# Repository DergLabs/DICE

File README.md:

# DICE - Dynamic Image Compression Engine
<ins>Developed by John Hofmeyr, Claudia Oufft, Michael Haahr, Shahriyar Shawon, Oscar Balan</ins>

*Drexel University Senior Class of 2025*

*Developed under the guidance of Dr. Anup Das*

<ins>**Overview**</ins>

The goal of this project was to develop a hardware based image processing system and hybrid file format that would take advantage of the benefits from both lossy and lossless image compression. 

By utilizing tiling, different image compression formats can be applied throughout an image based on the content of the tile. Improved image quality can be obtained when comapred to fully lossy compression, while maintaining file sizes smaller than that of fully lossless images. Our proposed solution utilizes a hardware optimized JPEG encoder for lossy compression and a novel hardware optimized arithmetic encoder for lossless compression.

<ins>**Implementation**</ins>

Image files are loaded and pre-processed into a pixel datastream using the Dice Reference compression tool. Image pre-processing consists of extracting the R, G and B channels from the image, applying matrix folding to create the 32x32 pixel tiles, and finally creating the byte arrays of raw pixels to be sent to the FPGA via USB. 

The FT600 USB FIFO is used to send and receive image data. Raw image data is sent to the FPGA module and loaded into a CDC FIFO buffer. The buffer stores 4KB of pixel data (equivalent to a 32x32 tile using 32b per pixel (8b for R, G, B and one spare byte to simplify processing). 

The pixels are then sent to the hardware statistics core to compute the mean, variance and std. deviation of the Laplacian and X/Y gradient kernels. The Variance of the Laplacian kernel values provides a numerical value that quantifies the blurryness of the tile while the mean and std. deviation of the 2d X/Y gradient values provide an indication of large changes in contrast, color or sharp edges in the tile. This information is used to determine what compression method should be used based on pre-defined threshold values. 

While the tile statistics are calculated, the pixel data is sent to both the Lossy and Lossless compression cores, with the processed data being buffered in output hold ram. Once the compression determination is made, the output data streams from both hold rams are muxed, selecting only one to be transmitted back to the FT600. 

<ins>**Hardware Platform**</ins> 

A dual board hardware platform was developed for this project. The hardware architecture is split into two modules, the IO moduel and FPGA module. The IO module provides video connectivity, high speed USB connectivity, USB-PD power control and monitoring, and Debug/JTAG IO. Below is a list of all IO available: 

- 4 Lane MIPI CSI (upto 2Gb/s per lane)
- HDMI 2.0 (Upto 4K 30FPS via Sii1136)
- USB 3.0 5Gb/s to FT600
- 3x USB 2.0 (1x for RP2040, 1x for FT2232, 1x for FPGA module MCU)
- Configurable USB-PD control allowing for upto 15V 5A
- Voltage, Current, Power & Temperature monitoring
- UART & JTAG for FPGA
- 12x GPIOs from RP2040 MCU to FPGA
- 16-bit USB FIFO Bus to FPGA (upto 1Gb/s)

The FPGA Module provides all of the processing hardware and implements the custom designed image processor. A Xilinx Kintex Ultrascale+ KU3P was utilized. Two DC-DC converters generate all voltage rails, the TDA38840 provides 0.85V at upto 40A for the FPGA VCCINT, and an LT7200 is used to generate 3.3V, 5V, 1.8V and 1.2V at 3A per channel. All rails have voltage, current, power and temperature monitoring. An onboard 200MHz oscillator provides the main system clock for the FPGA. Four 512Mb HyperRam 3.0 memory modules are also present. Each memory chip provides a 16-bit 250MHz DDR bus. The memory chips have been routed to allow for two banks of two chips each with length matching between chips 0/1 and 2/3. 

<ins>**Hardware Architecture**</ins>

The harware platform is split between two modules; the IO module and the FPGA module. The IO module contains all user IO, USB Power handling and supporting interface hardware. The FPGA module contains the Kintex US+ KU3P FPGA, 4x HyperRam modules, power supplies, FPGA clock, and onboard microcontroller. 

*IO Module Specifications*
- USB-C 3.0 Data & Power Port, supports 5Gb/s USB & USB-PD 2.1 (upto 20V 5A)
- 4 lane MIPI CSI
- HDMI 1.4b, supports 4K30
- FT600 USB FIFO, supports 1Gb/s bandwidth over 16-bit bus
- FT2232 confgired for JTAG and UART
- RP2040 for data logging & control

*FPGA Module Specifications*
- Kintex Ultrascale+ KU3P FPGA
- 4x HyperRam 3.0 512Mb
- RP2040 MCU
- LT7200S DC-DC (1.8v, 1.2v, 3.3v, 5v at 3A each)
- TDA38840A DC-DC (0.85V VCCINT at 40A)
- INA700 power monitors on 1.8v, 1.2v, 3.3v
- INA236 power monitor on 0.85V
- 4x User LED's
- 8x GPIO debug pads
- 200MHz System Clock
- 256Mb configuration memory

The following diagram outlines the top level hardware configuration:

<ins>**Lossy Compression Architecture**</ins>

The lossy compression method implemented for this design is a hardware optimized version of JPEG encoding. The JPEG implementation has been designed to work on 8 pixels per clock cycle, using a serial-to-parallel input register to convert the serial pixel input stream into 8 parallel pixel streams. The simplified architecture for the lossy core is shown below.

In addition to the JPEG compression core, RGB to YCrCb conversion is performed. The implementation for this is shown below.

In order to determine which compression method to utilize, statistics from the gradient and laplacian kernels is used. The current implementation uses the variance of the X/Y gradient and Laplacian convolutions. Variance was chosen as it provides a good representation of texture, edge transitions, and blur. The implementation of the gradient and laplacian calculations are shown below. Note, only the X sobel computation is shown, however the Y computation is identical.

<ins>Laplacian Core</ins>

<ins>Gradient Core</ins>

<ins>**Lossless Compression Architecture**</ins>

<ins>Arithmetic Encoder Core</ins>

For the lossless compression core, a running count adaptive model is used since arithmetic encoding can achieve a higher compression ratio using applicable adaptive models. Data can be ingested and processed at a rate of one byte per clock cycle. A binary tree for storing symbol probability ranges was chosen to reduce the lookup time for the lower bound of the range to O(lg(n)), where n is the bit-width of the symbol. Choosing 8 bits as the symbol size was done to ensure large enough symbols could be processed by the arithmetic compression core, but would not be so large as to make the size of the binary tree for storing the probability ranges of each symbol too big. 

A data dependency between the upper and lower working range of the encoder and the output of the final renormalization stages of the pipeline could result in stalling for several clock cycles while waiting for the updated ranges. Some reorganization and consolidation of the pipeline was done to reduce the length of this dependency in the pipeline, such as moving the division step of the new bounds calculation before this critical path, and reducing the renormalization steps to take one cycle each. The final step employed to overcome stalling in the critical path of the arithmetic coding pipeline is to use multiple working bounds. This effectively strobes the data into multiple compression streams that share the same pipeline, negating the need to stall as long as the number of streams is higher than the number of pipeline stages in the critical path.

A top level architecture diagram of the arithemetic encoder is shown below.

<ins>**Software Tools**</ins>

Two main software tools are used; the serial communications tool, and the reference compression tool. 

The serial communications tool provides a serial terminal for connecting to the onboard microcontrollers. This terminal displays important hardware metrics including board temperatures, voltages, currents and power of the various power rails. 

The reference compression tool is used to test and use the DICE hardware. This tool allows users to load in an image, set gradient and laplacian threshold values, format and transfer image data to the FPGA, decode recieved image data, create and save the DICE image files, and display the DICE compressed image with relevant statistics such as PSNR, MS-SSIM, file size and lossy/lossless tile metrics. 

<ins>**DICE File Format**</ins>

The DICE file format is broken into three main sections; the main file header, the lossless header and lossless data, and the lossy header and lossy data. The main file header contains general file information, decoding and dequantization tables as well as the tile ID grid used to identify the location and ID of each image tile. The lossy and lossless headers provide information about the number of tiles, and the size of each tile. All tiles are formatted to be the same size for simplicity sake, however future improvements would include allowing for variable tile sizes to reduce file size. Finally, the lossless tiles are stored as arithmetic encoded R, G and B arrays while the Lossy data is stored as quantized Y, Cr and Cb arrays. The diagram below shows the full file format.

<ins>DICE File Format</ins>

<ins>**Research Papers & References**</ins>

The following research papers and references were used during the development of this project.

[1] Jonathan Griffin,
“The Ultimate Guide to JPEG including JPEG Compression & Encoding”
www.thewebmaster.com. https://www.thewebmaster.com/jpeg-definitive-guide/

‌
[2]H. Anas, “Fast 8*8*8 RCF 3D_DCT/IDCT transform for real time video compression and its FPGA Implementation,” vol. volume 7, no. 2, May 2014, https://www.researchgate.net/publication/262896207_Fast_888_RCF_3D_DCTIDCT_transform_for_real_time_video_compression_and_its_FPGA_Implementation
‌

[3]H. Anas, Said Belkouch, M. El Aakif, and Noureddine Chabini, “FPGA implementation of a pipelined 2D-DCT and simplified quantization for real-time applications,” International Conference on Multimedia Computing and Systems, pp. 1–6, Apr. 2011, doi: https://doi.org/10.1109/icmcs.2011.5945659.
‌

[4]S. Sudiro, A. Kardian, S. Madenda, and L. Hermanto, “OPEN ACCESS Mean and variance statistic for image processing on FPGA,” vol. 115, no. 1, p. 2020115, doi: https://doi.org/10.6703/IJASE.202103_18(1).115.
‌

‌[5] Mark Nelson,
“Data Compression With Arithmetic Coding”, Mark Nelson, Oct. 19, 2014.
https://marknelson.us/posts/2014/10/19/data-compression-with-arithmetic-coding.html 

‌[6] Mark Nelson,
“Arithmetic Coding + Statistical Modeling = Data Compression”, Mark Nelson, Feb. 1, 1991.
https://marknelson.us/posts/1991/02/01/arithmetic-coding-statistical-modeling-data-compression

‌[7] Wikipedia Contributors,
“Discrete Cosine Transform”, Wikipedia,
https://en.wikipedia.org/wiki/Discrete_cosine_transform# 

[8] Wikipedia Contributors,
“Huffman Coding”, Wikipedia,
https://en.wikipedia.org/wiki/Huffman_coding 
‌

‌[9]
“LZSS” The Hitchhiker’s Guide to Compression, 2024.
https://go-compression.github.io/algorithms/lzss/

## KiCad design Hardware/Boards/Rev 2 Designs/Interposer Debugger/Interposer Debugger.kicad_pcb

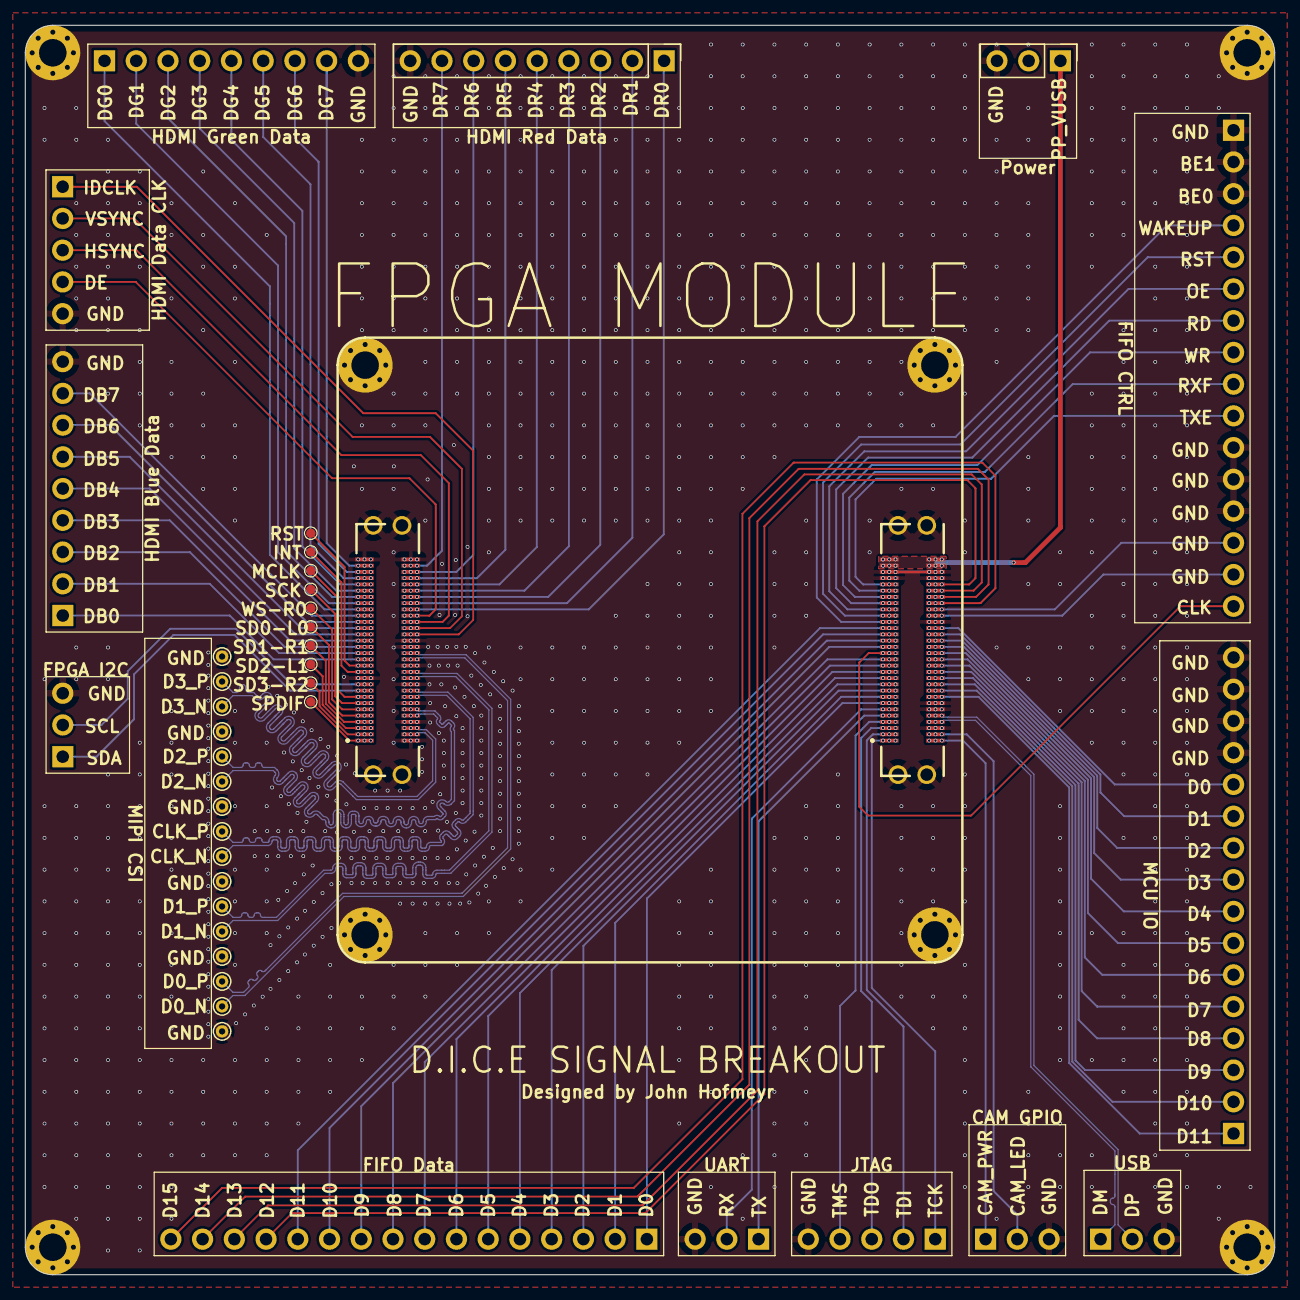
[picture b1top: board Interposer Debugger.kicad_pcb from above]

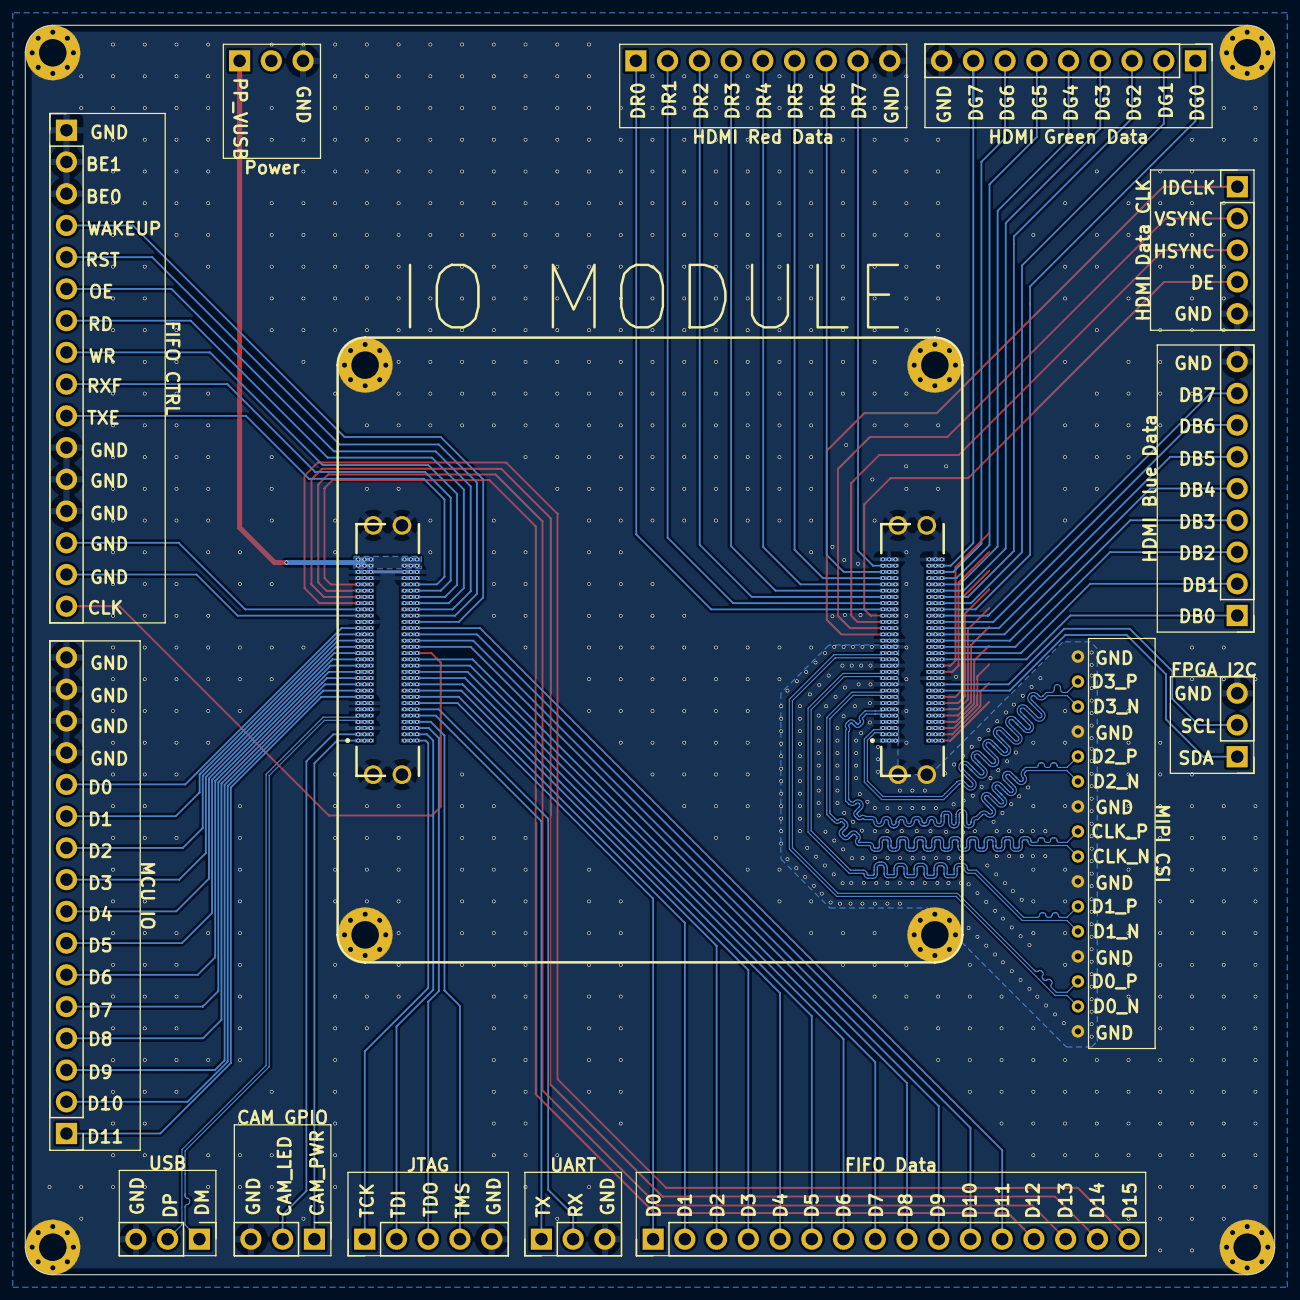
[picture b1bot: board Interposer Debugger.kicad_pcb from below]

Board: 4 copper layers, 100.0 x 100.0 mm, 51 parts (13 on the bottom side), 100 nets.

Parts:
J1, J16: Conn_01x05; PinHeader_1x05_P2.54mm_Vertical
J2, J3, J4, J5: LSHM-130-XX.X-XXX-DV-A-S-K-XX; SAMTEC_LSHM-130-XX.X-XXX-DV-A-S-K-XX
J7, J14, J19, J21, J22: Conn_01x03; PinHeader_1x03_P2.54mm_Vertical
J8, J23, J24: Conn_01x16; PinHeader_1x16_P2.54mm_Vertical
J9, J12, J13: Conn_01x09; PinHeader_1x09_P2.54mm_Vertical
TP1, TP2, TP3, TP4: Mounting Hole; MountingHole_2.2mm_M2_Pad_Via
TP5, TP6, TP7#2, TP8, TP9#2, TP10, TP11, TP12, TP13, TP14: TestPoint; Test Point 0.75mm
TP6#2, TP7, TP8#2, TP9: MH; MountingHole_2.2mm_M2_Pad_Via
TP15, TP16, TP17, TP18, TP19, TP20, TP21, TP22, TP23, TP24, TP25, TP26, TP27, TP28, TP29, TP30: TestPoint; TestPoint_THTPad_D1.0mm_Drill0.5mm

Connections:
/CAM_LED_EN: J3.04, J5.03, J19.2
/CAM_PWR_EN: J3.02, J5.01, J19.1
/FIFO_BE0: J3.44, J5.43, J23.14
/FIFO_BE1: J3.42, J5.41, J23.15
/FIFO_CLK: J3.29, J5.30, J23.16
/FIFO_D0: J3.13, J5.14, J8.1
/FIFO_D1: J3.15, J5.16, J8.2
/FIFO_D2: J3.17, J5.18, J8.3
/FIFO_D3: J3.19, J5.20, J8.4
/FIFO_D4: J3.21, J5.22, J8.5
/FIFO_D5: J3.23, J5.24, J8.6
/FIFO_D6: J3.25, J5.26, J8.7
/FIFO_D7: J3.27, J5.28, J8.8
/FIFO_D8: J3.31, J5.32, J8.9
/FIFO_D9: J3.33, J5.34, J8.10
/FIFO_D10: J3.35, J5.36, J8.11
/FIFO_D11: J3.37, J5.38, J8.12
/FIFO_D12: J3.52, J5.51, J8.13
/FIFO_D13: J3.50, J5.49, J8.14
/FIFO_D14: J3.48, J5.47, J8.15
/FIFO_D15: J3.46, J5.45, J8.16
/FPGA_I2C_SCL: J2.19, J4.20, J14.2
/FPGA_I2C_SDA: J2.17, J4.18, J14.1
/FT600_OE: J3.47, J5.48, J23.8
/FT600_RD: J3.45, J5.46, J23.7
/FT600_RST: J3.49, J5.50, J23.9
/FT600_RXE: J3.41, J5.42, J23.5
/FT600_TXE: J3.39, J5.40, J23.4
/FT600_WAKEUP: J3.51, J5.52, J23.10
/FT600_WR: J3.43, J5.44, J23.6
/HDMI_DB0: J2.27, J4.28, J13.1
/HDMI_DB1: J2.29, J4.30, J13.2
/HDMI_DB2: J2.31, J4.32, J13.3
/HDMI_DB3: J2.33, J4.34, J13.4
/HDMI_DB4: J2.35, J4.36, J13.5
/HDMI_DB5: J2.37, J4.38, J13.6
/HDMI_DB6: J2.39, J4.40, J13.7
/HDMI_DB7: J2.41, J4.42, J13.8
/HDMI_DE: J2.42, J4.41, J16.4
/HDMI_DG0: J2.43, J4.44, J12.1
/HDMI_DG1: J2.45, J4.46, J12.2
/HDMI_DG2: J2.47, J4.48, J12.3
/HDMI_DG3: J2.49, J4.50, J12.4
/HDMI_DG4: J2.51, J4.52, J12.5
/HDMI_DG5: J2.53, J4.54, J12.6
/HDMI_DG6: J2.55, J4.56, J12.7
/HDMI_DG7: J2.57, J4.58, J12.8
/HDMI_DR0: J2.44, J4.43, J9.1
/HDMI_DR1: J2.46, J4.45, J9.2
/HDMI_DR2: J2.48, J4.47, J9.3
/HDMI_DR3: J2.50, J4.49, J9.4
/HDMI_DR4: J2.52, J4.51, J9.5
/HDMI_DR5: J2.54, J4.53, J9.6
/HDMI_DR6: J2.56, J4.55, J9.7
/HDMI_DR7: J2.58, J4.57, J9.8
/HDMI_HSYNC: J2.40, J4.39, J16.3
/HDMI_IDCLK: J2.36, J4.35, J16.1
/HDMI_INT: J2.23, J4.24, TP13.1
/HDMI_MCLK: J2.15, J4.16, TP12.1
/HDMI_RST: J2.25, J4.26, TP14.1
/HDMI_SCK: J2.13, J4.14, TP11.1
/HDMI_SD0_DL0: J2.09, J4.10, TP9#2.1
/HDMI_SD1_DR1: J2.07, J4.08, TP8.1
/HDMI_SD2_DL1: J2.05, J4.06, TP7#2.1
/HDMI_SD3_DR2: J2.03, J4.04, TP6.1
/HDMI_SPDIF: J2.01, J4.02, TP5.1
/HDMI_VSYNC: J2.38, J4.37, J16.2
/HDMI_WS_DR0: J2.11, J4.12, TP10.1
/JTAG_TCK: J1.1, J3.01, J5.02
/JTAG_TDI: J1.2, J3.03, J5.04
/JTAG_TDO: J1.3, J3.05, J5.06
/JTAG_TMS: J1.4, J3.07, J5.08
/MBUS_D0: J3.38, J5.37, J24.12
/MBUS_D1: J3.36, J5.35, J24.11
/MBUS_D2: J3.34, J5.33, J24.10
/MBUS_D3: J3.32, J5.31, J24.9
/MBUS_D4: J3.30, J5.29, J24.8
/MBUS_D5: J3.28, J5.27, J24.7
/MBUS_D6: J3.26, J5.25, J24.6
/MBUS_D7: J3.24, J5.23, J24.5
/MBUS_D8: J3.22, J5.21, J24.4
/MBUS_D9: J3.20, J5.19, J24.3
/MBUS_D10: J3.18, J5.17, J24.2
/MBUS_D11: J3.16, J5.15, J24.1
/MIPI_CLK_N: J2.18, J4.17, TP23.1
/MIPI_CLK_P: J2.16, J4.15, TP22.1
/MIPI_D0_N: J2.30, J4.29, TP29.1
/MIPI_D0_P: J2.28, J4.27, TP28.1
/MIPI_D1_N: J2.24, J4.23, TP26.1
/MIPI_D1_P: J2.22, J4.21, TP25.1
/MIPI_D2_N: J2.12, J4.11, TP20.1
/MIPI_D2_P: J2.10, J4.09, TP19.1
/MIPI_D3_N: J2.06, J4.05, TP17.1
/MIPI_D3_P: J2.04, J4.03, TP16.1
/PP_VUSB: J3.57, J3.58, J3.59, J3.60, J5.57, J5.58, J5.59, J5.60, J7.1
/UART_RX: J3.11, J5.12, J21.2
/UART_TX: J3.09, J5.10, J21.1
/USB_SYSMON_D_N: J3.08, J5.07, J22.1
/USB_SYSMON_D_P: J3.10, J5.09, J22.2
GND: J1.5, J2.02, J2.08, J2.14, J2.20, J2.21, J2.26, J2.32, J2.34, J2.59, J2.60, J2.S1 (SHIELD), J2.S2 (SHIELD__1), J3.06, J3.12, J3.14, J3.40, J3.53, J3.54, J3.55, J3.56, J3.S1 (SHIELD), J3.S2 (SHIELD__1), J4.01, J4.07, J4.13, J4.19, J4.22, J4.25, J4.31, J4.33, J4.59, J4.60, J4.S1 (SHIELD), J4.S2 (SHIELD__1), J5.05, J5.11, J5.13, J5.39, J5.53, J5.54, J5.55, J5.56, J5.S1 (SHIELD), J5.S2 (SHIELD__1), J7.3, J9.9, J12.9, J13.9, J14.3, J16.5, J19.3, J21.3, J22.3, J23.1, J23.2, J23.3, J23.11, J23.12, J23.13, J24.13, J24.14, J24.15, J24.16, TP1.1, TP2.1, TP3.1, TP4.1, TP6#2.1, TP7.1, TP8#2.1, TP9.1, TP15.1, TP18.1, TP21.1, TP24.1, TP27.1, TP30.1

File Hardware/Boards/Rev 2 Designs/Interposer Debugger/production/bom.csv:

Designator,Footprint,Quantity,Value,LCSC Part #
"J1, J16",PinHeader_1x05_P2.54mm_Vertical,2,Conn_01x05,
"J12, J13, J9",PinHeader_1x09_P2.54mm_Vertical,3,Conn_01x09,
"J14, J19, J21, J22, J7",PinHeader_1x03_P2.54mm_Vertical,5,Conn_01x03,
"J2, J3, J4, J5",SAMTEC_LSHM-130-XX.X-XXX-DV-A-S-K-XX,4,LSHM-130-XX.X-XXX-DV-A-S-K-XX,
"J23, J24, J8",PinHeader_1x16_P2.54mm_Vertical,3,Conn_01x16,
"TP1, TP2, TP3, TP4",MountingHole_2.2mm_M2_Pad_Via,4,Mounting Hole,
"TP10, TP11, TP12, TP13, TP14, TP5, TP6_2, TP7, TP8_2, TP9",Test Point 0.75mm,10,TestPoint,
"TP15, TP16, TP17, TP18, TP19, TP20, TP21, TP22, TP23, TP24, TP25, TP26, TP27, TP28, TP29, TP30",TestPoint_THTPad_D1.0mm_Drill0.5mm,16,TestPoint,
"TP6, TP7_2, TP8, TP9_2",MountingHole_2.2mm_M2_Pad_Via,4,MH,

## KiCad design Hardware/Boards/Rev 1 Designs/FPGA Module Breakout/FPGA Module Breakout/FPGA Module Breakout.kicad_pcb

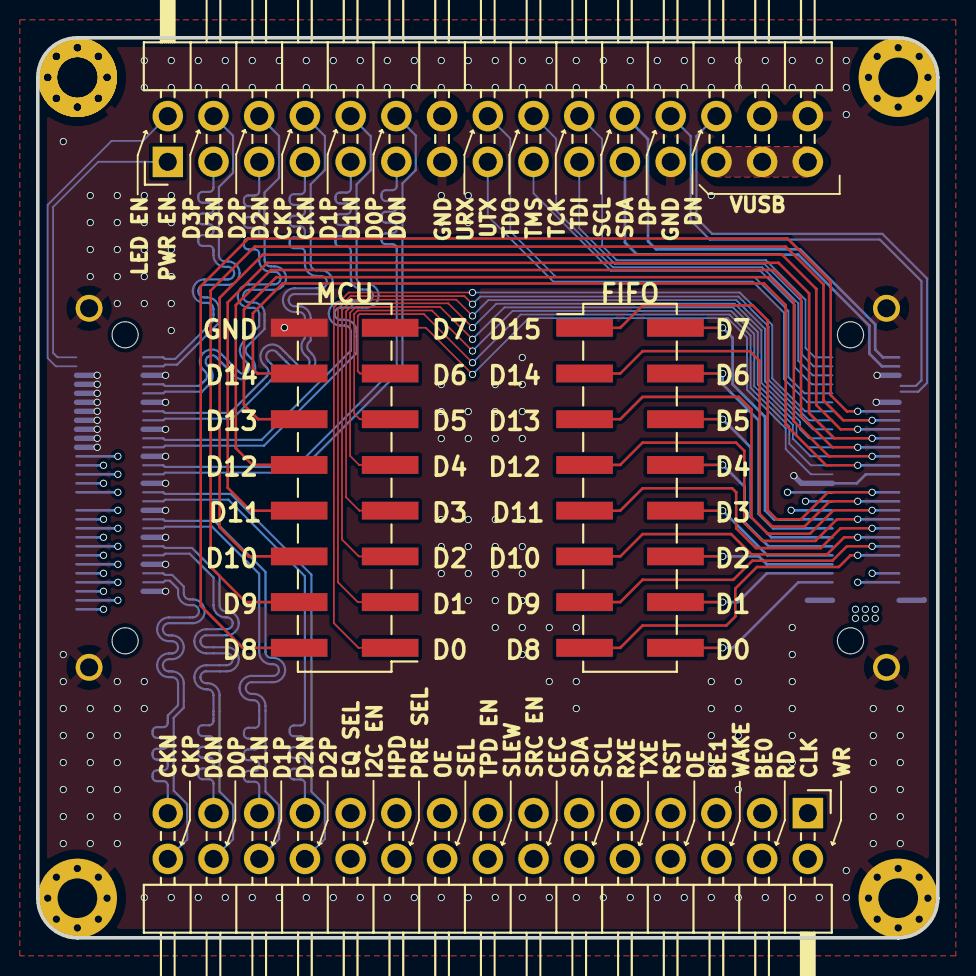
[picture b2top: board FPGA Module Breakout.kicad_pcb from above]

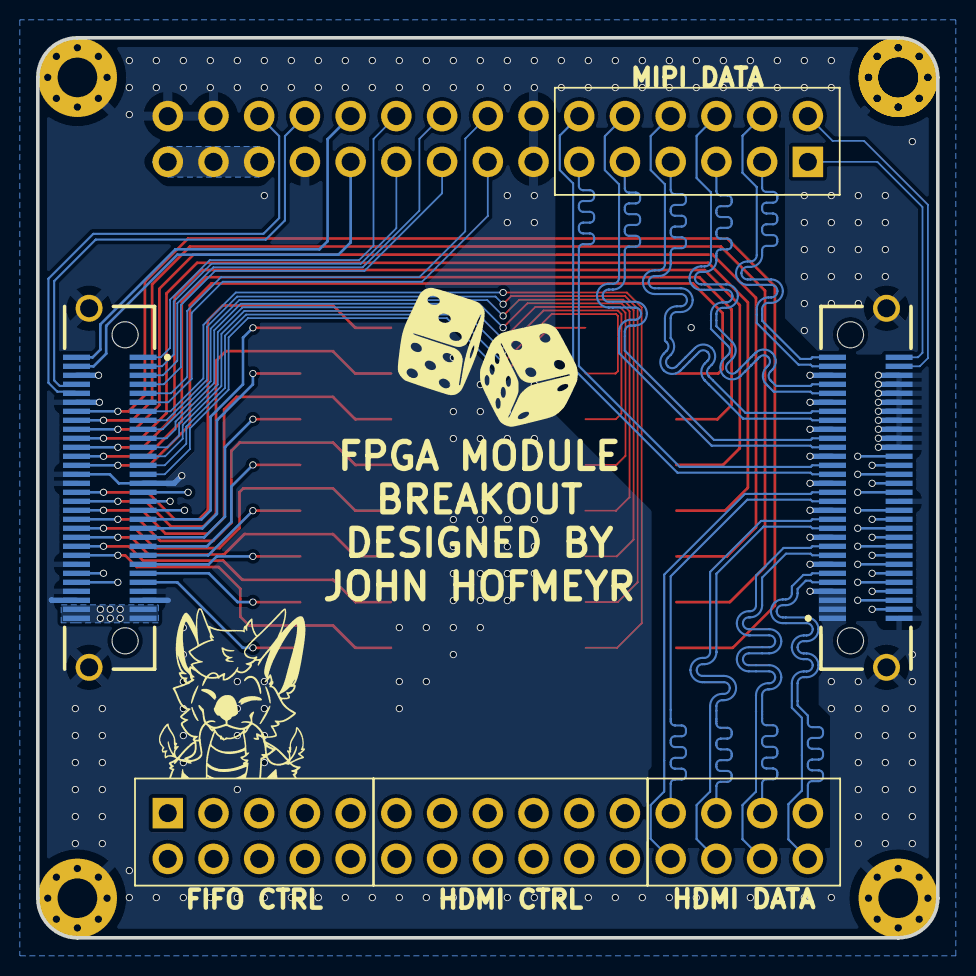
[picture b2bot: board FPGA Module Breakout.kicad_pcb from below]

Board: 4 copper layers, 50.0 x 50.0 mm, 11 parts (2 on the bottom side), 85 nets.

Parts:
J1, J2: LSHM-130-XX.X-XXX-DV-A-S-K-XX; SAMTEC_LSHM-130-XX.X-XXX-DV-A-S-K-XX
J3, J18: Conn_02x08_Odd_Even; PinHeader_2x08_P2.54mm_Vertical_SMD
J4, J5: Conn_02x15_Odd_Even; PinHeader_2x15_P2.54mm_Horizontal
PCB: Mounting Hole; MountingHole_2.2mm_M2_Pad_Via
TP1, TP2, TP3, TP4: Mounting Hole; MountingHole_2.2mm_M2_Pad_Via

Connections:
/CAM_LED_EN: J1.58, J5.2
/CAM_PWR_EN: J1.60, J5.1
/FIFO_BE0: J2.33, J4.3
/FIFO_BE1: J2.31, J4.5
/FIFO_CLK: J2.35, J4.1
/FIFO_D0: J2.51, J18.16
/FIFO_D1: J2.49, J18.14
/FIFO_D2: J2.47, J18.12
/FIFO_D3: J2.45, J18.10
/FIFO_D4: J2.43, J18.8
/FIFO_D5: J2.41, J18.6
/FIFO_D6: J2.39, J18.4
/FIFO_D7: J2.37, J18.2
/FIFO_D8: J2.46, J18.15
/FIFO_D9: J2.44, J18.13
/FIFO_D10: J2.42, J18.11
/FIFO_D11: J2.40, J18.9
/FIFO_D12: J2.38, J18.7
/FIFO_D13: J2.36, J18.5
/FIFO_D14: J2.34, J18.3
/FIFO_D15: J2.32, J18.1
/FPGA_I2C_SCL: J2.02, J5.22
/FPGA_I2C_SDA: J2.04, J5.21
/FT600_OE: J1.34, J4.8
/FT600_RD: J2.50, J4.4
/FT600_RST: J1.36, J4.7
/FT600_RXE: J1.32, J4.9
/FT600_TXE: J1.30, J4.10
/FT600_WAKEUP: J1.38, J4.6
/FT600_WR: J2.52, J4.2
/HDMI_CEC: J1.20, J4.14
/HDMI_CLK_N: J1.09, J4.29
/HDMI_CLK_P: J1.11, J4.30
/HDMI_D0_N: J1.15, J4.27
/HDMI_D0_P: J1.17, J4.28
/HDMI_D1_N: J1.21, J4.25
/HDMI_D1_P: J1.23, J4.26
/HDMI_D2_N: J1.27, J4.23
/HDMI_D2_P: J1.29, J4.24
/HDMI_EQ_SEL: J1.06, J4.21
/HDMI_HPD_SRC: J1.10, J4.19
/HDMI_I2C_EN: J1.04, J4.22
/HDMI_OE: J1.14, J4.17
/HDMI_PRE_SEL: J1.08, J4.20
/HDMI_SCL_SRC: J1.24, J4.12
/HDMI_SDA_SRC: J1.26, J4.11
/HDMI_SDA_SRC_EN: J1.22, J4.13
/HDMI_SEL: J1.12, J4.18
/HDMI_SLEW_CTL: J1.16, J4.16
/JTAG_TCK: J2.01, J5.20
/JTAG_TDI: J2.03, J5.19
/JTAG_TDO: J2.05, J5.18
/JTAG_TMS: J2.07, J5.17
/MBUS_D0: J2.13, J3.1
/MBUS_D1: J2.15, J3.3
/MBUS_D2: J2.17, J3.5
/MBUS_D3: J2.19, J3.7
/MBUS_D4: J2.21, J3.9
/MBUS_D5: J2.23, J3.11
/MBUS_D6: J2.25, J3.13
/MBUS_D7: J2.27, J3.15
/MBUS_D8: J2.14, J3.2
/MBUS_D9: J2.16, J3.4
/MBUS_D10: J2.18, J3.6
/MBUS_D11: J2.20, J3.8
/MBUS_D12: J2.22, J3.10
/MBUS_D13: J2.24, J3.12
/MBUS_D14: J2.26, J3.14
/MIPI_CLK_N: J1.47, J5.7
/MIPI_CLK_P: J1.45, J5.8
/MIPI_D0_N: J1.35, J5.11
/MIPI_D0_P: J1.33, J5.12
/MIPI_D1_N: J1.41, J5.9
/MIPI_D1_P: J1.39, J5.10
/MIPI_D2_N: J1.53, J5.5
/MIPI_D2_P: J1.51, J5.6
/MIPI_D3_N: J1.59, J5.3
/MIPI_D3_P: J1.57, J5.4
/PP_VUSB: J2.57, J2.58, J2.59, J2.60, J5.25, J5.27, J5.29
/TPD5_EN: J1.18, J4.15
/UART_RX: J2.09, J5.16
/UART_TX: J2.11, J5.15
/USB_SYSMON_D_N: J2.10, J5.26
/USB_SYSMON_D_P: J2.08, J5.24
GND: J1.01, J1.02, J1.03, J1.05, J1.07, J1.13, J1.19, J1.25, J1.28, J1.31, J1.37, J1.40, J1.42, J1.43, J1.44, J1.46, J1.48, J1.49, J1.50, J1.52, J1.54, J1.55, J1.56, J1.S1 (SHIELD), J1.S2 (SHIELD__1), J2.06, J2.12, J2.28, J2.29, J2.30, J2.48, J2.53, J2.54, J2.55, J2.56, J2.S1 (SHIELD), J2.S2 (SHIELD__1), J3.16, J5.13, J5.14, J5.23, J5.28, J5.30, TP1.1, TP2.1, TP3.1, TP4.1

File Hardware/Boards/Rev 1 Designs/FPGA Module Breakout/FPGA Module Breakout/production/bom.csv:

Designator,Footprint,Quantity,Value,LCSC Part #
"J1, J2",SAMTEC_LSHM-130-XX.X-XXX-DV-A-S-K-XX,2,LSHM-130-XX.X-XXX-DV-A-S-K-XX,
"J18, J3",PinHeader_2x08_P2.54mm_Vertical_SMD,2,Conn_02x08_Odd_Even,
"J4, J5",PinHeader_2x15_P2.54mm_Horizontal,2,Conn_02x15_Odd_Even,
"PCB, TP1, TP2, TP3, TP4",MountingHole_2.2mm_M2_Pad_Via,5,Mounting Hole,

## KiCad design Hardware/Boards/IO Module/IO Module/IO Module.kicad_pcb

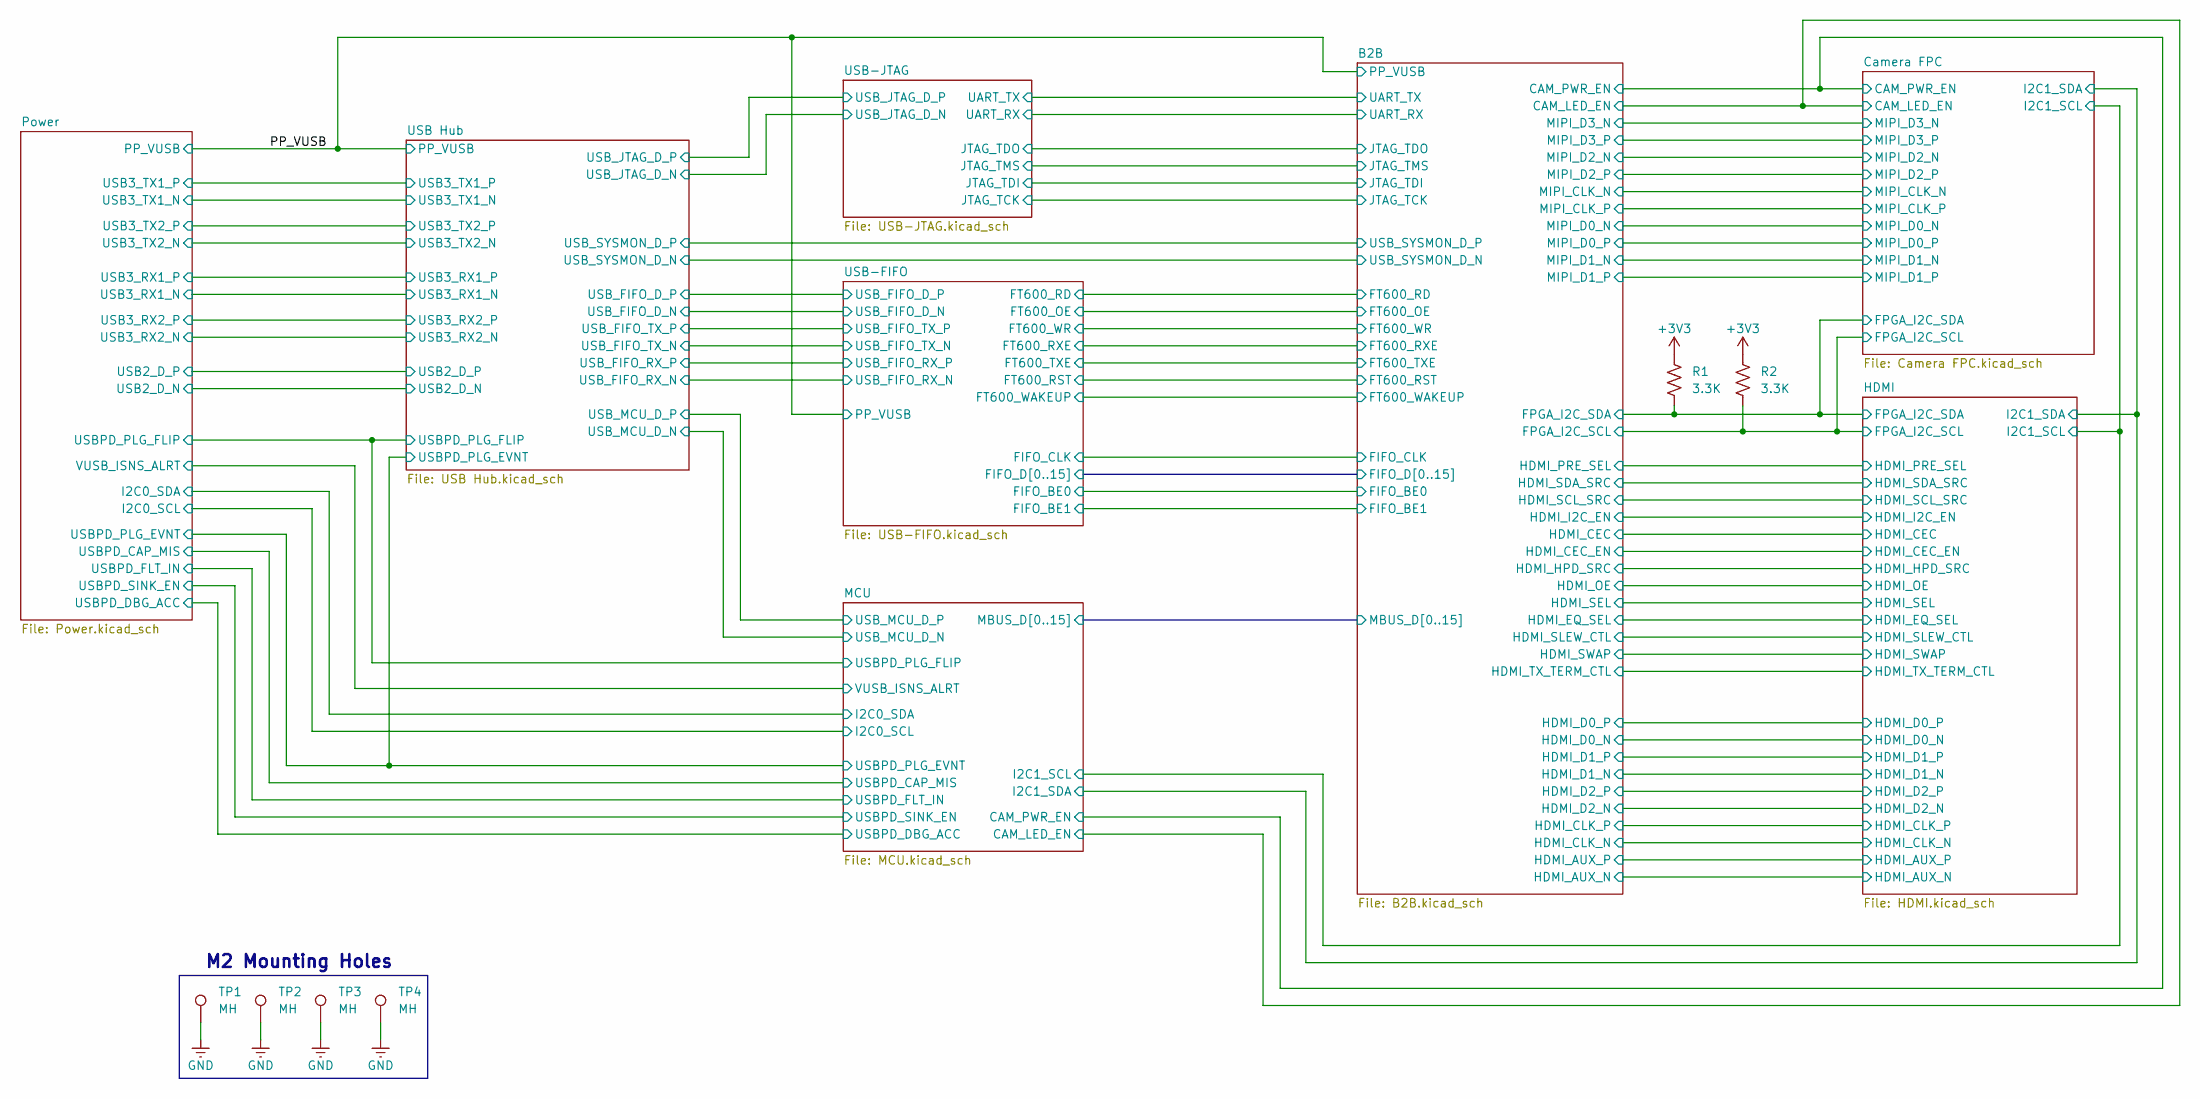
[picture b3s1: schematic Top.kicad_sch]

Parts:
R1, R2: 3.3K; R_0201_0603Metric
TP1, TP2, TP3, TP4: MH; MountingHole_2.2mm_M2_Pad_Via

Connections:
+3V3: R1.2, R2.2; also elsewhere on the board
/Top/B2B/FPGA_I2C_SCL: R2.1; also elsewhere on the board
/Top/B2B/FPGA_I2C_SDA: R1.1; also elsewhere on the board
GND: TP1.1, TP2.1, TP3.1, TP4.1; also elsewhere on the board

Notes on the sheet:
M2 Mounting Holes

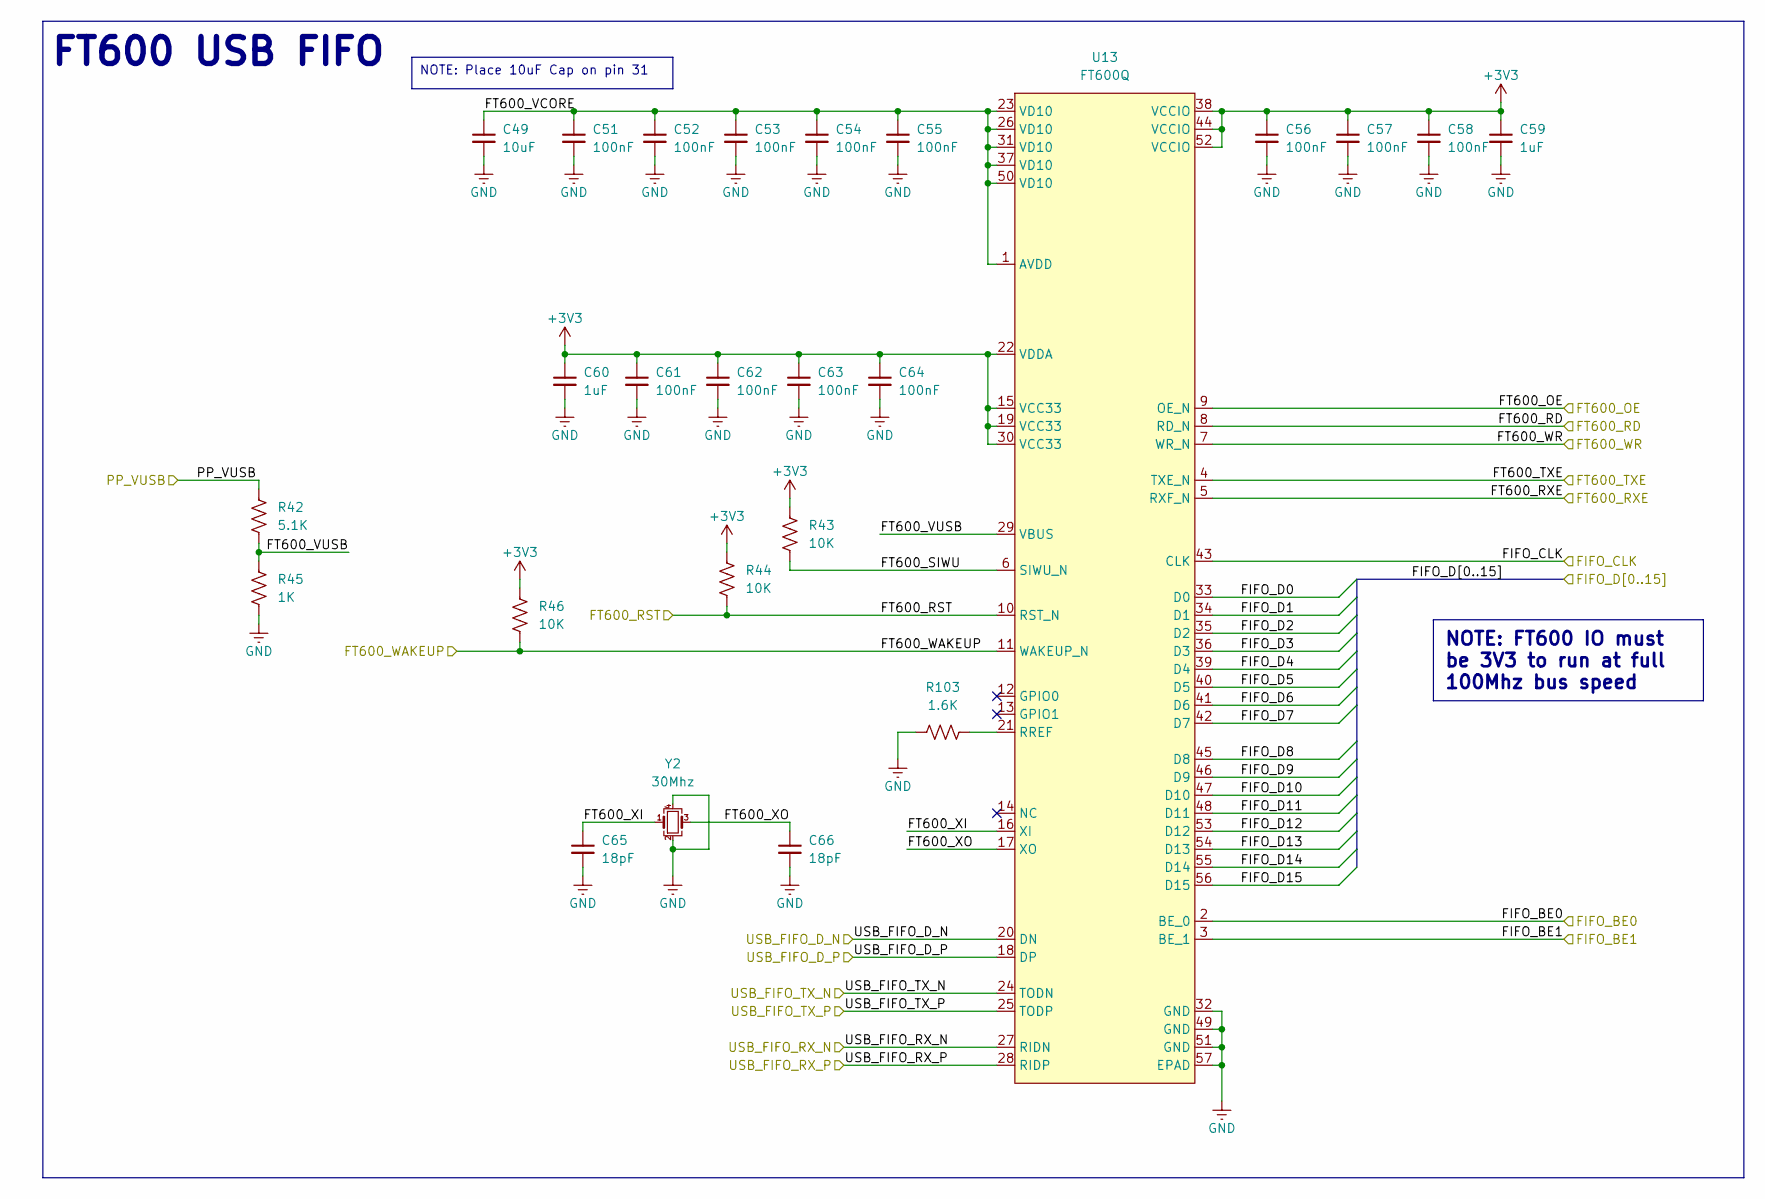
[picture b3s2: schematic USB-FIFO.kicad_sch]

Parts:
C49: 10uF; C_0603_1608Metric
C51, C52, C53, C54, C55, C56, C57, C58, C61, C62, C63, C64: 100nF; C_0201_0603Metric
C59, C60: 1uF; C_0201_0603Metric
C65, C66: 18pF; C_0201_0603Metric
R42: 5.1K; R_0201_0603Metric
R43, R44, R46: 10K; R_0201_0603Metric
R45: 1K; R_0201_0603Metric
R103: 1.6K; R_0201_0603Metric
U13: FT600Q; QFN-56-1EP_7x7mm_P0.4mm_EP4x4mm
Y2: 30Mhz; Oscillator_SMD_Abracon_ASE-4Pin_3.2x2.5mm

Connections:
+3V3: C56.1, C57.1, C58.1, C59.1, C60.1, C61.1, C62.1, C63.1, C64.1, R43.2, R44.2, R46.2, U13.15 (VCC33), U13.19 (VCC33), U13.22 (VDDA), U13.30 (VCC33), U13.38 (VCCIO), U13.44 (VCCIO), U13.52 (VCCIO); also elsewhere on the board
/Top/B2B/FIFO_BE0: U13.2 (BE_0); also elsewhere on the board
/Top/B2B/FIFO_BE1: U13.3 (BE_1); also elsewhere on the board
/Top/B2B/FIFO_CLK: U13.43 (CLK); also elsewhere on the board
/Top/B2B/FIFO_D0: U13.33 (D0); also elsewhere on the board
/Top/B2B/FIFO_D1: U13.34 (D1); also elsewhere on the board
/Top/B2B/FIFO_D2: U13.35 (D2); also elsewhere on the board
/Top/B2B/FIFO_D3: U13.36 (D3); also elsewhere on the board
/Top/B2B/FIFO_D4: U13.39 (D4); also elsewhere on the board
/Top/B2B/FIFO_D5: U13.40 (D5); also elsewhere on the board
/Top/B2B/FIFO_D6: U13.41 (D6); also elsewhere on the board
/Top/B2B/FIFO_D7: U13.42 (D7); also elsewhere on the board
/Top/B2B/FIFO_D8: U13.45 (D8); also elsewhere on the board
/Top/B2B/FIFO_D9: U13.46 (D9); also elsewhere on the board
/Top/B2B/FIFO_D10: U13.47 (D10); also elsewhere on the board
/Top/B2B/FIFO_D11: U13.48 (D11); also elsewhere on the board
/Top/B2B/FIFO_D12: U13.53 (D12); also elsewhere on the board
/Top/B2B/FIFO_D13: U13.54 (D13); also elsewhere on the board
/Top/B2B/FIFO_D14: U13.55 (D14); also elsewhere on the board
/Top/B2B/FIFO_D15: U13.56 (D15); also elsewhere on the board
/Top/B2B/FT600_OE: U13.9 (OE_N); also elsewhere on the board
/Top/B2B/FT600_RD: U13.8 (RD_N); also elsewhere on the board
/Top/B2B/FT600_RST: R44.1, U13.10 (RST_N); also elsewhere on the board
/Top/B2B/FT600_RXE: U13.5 (RXF_N); also elsewhere on the board
/Top/B2B/FT600_TXE: U13.4 (TXE_N); also elsewhere on the board
/Top/B2B/FT600_WAKEUP: R46.1, U13.11 (WAKEUP_N); also elsewhere on the board
/Top/B2B/FT600_WR: U13.7 (WR_N); also elsewhere on the board
/Top/PP_VUSB: R42.2; also elsewhere on the board
/Top/USB Hub/USB_FIFO_D_N: U13.20 (DN); also elsewhere on the board
/Top/USB Hub/USB_FIFO_D_P: U13.18 (DP); also elsewhere on the board
/Top/USB Hub/USB_FIFO_RX_N: U13.27 (RIDN); also elsewhere on the board
/Top/USB Hub/USB_FIFO_RX_P: U13.28 (RIDP); also elsewhere on the board
/Top/USB Hub/USB_FIFO_TX_N: U13.24 (TODN); also elsewhere on the board
/Top/USB Hub/USB_FIFO_TX_P: U13.25 (TODP); also elsewhere on the board
/Top/USB-FIFO/FT600_SIWU: R43.1, U13.6 (SIWU_N)
/Top/USB-FIFO/FT600_VCORE: C49.1, C51.1, C52.1, C53.1, C54.1, C55.1, U13.1 (AVDD), U13.23 (VD10), U13.26 (VD10), U13.31 (VD10), U13.37 (VD10), U13.50 (VD10)
/Top/USB-FIFO/FT600_VUSB: R42.1, R45.2, U13.29 (VBUS)
/Top/USB-FIFO/FT600_XI: C65.1, U13.16 (XI), Y2.1
/Top/USB-FIFO/FT600_XO: C66.1, U13.17 (XO), Y2.3
GND: C49.2, C51.2, C52.2, C53.2, C54.2, C55.2, C56.2, C57.2, C58.2, C59.2, C60.2, C61.2, C62.2, C63.2, C64.2, C65.2, C66.2, R45.1, R103.2, U13.32 (GND), U13.49 (GND), U13.51 (GND), U13.57 (EPAD), Y2.2, Y2.4; also elsewhere on the board
unnamed: R103.1, U13.21 (RREF)

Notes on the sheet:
NOTE: Place 10uF Cap on pin 31
NOTE: FT600 IO must be 3V3 to run at full 100Mhz bus speed
FT600 USB FIFO
